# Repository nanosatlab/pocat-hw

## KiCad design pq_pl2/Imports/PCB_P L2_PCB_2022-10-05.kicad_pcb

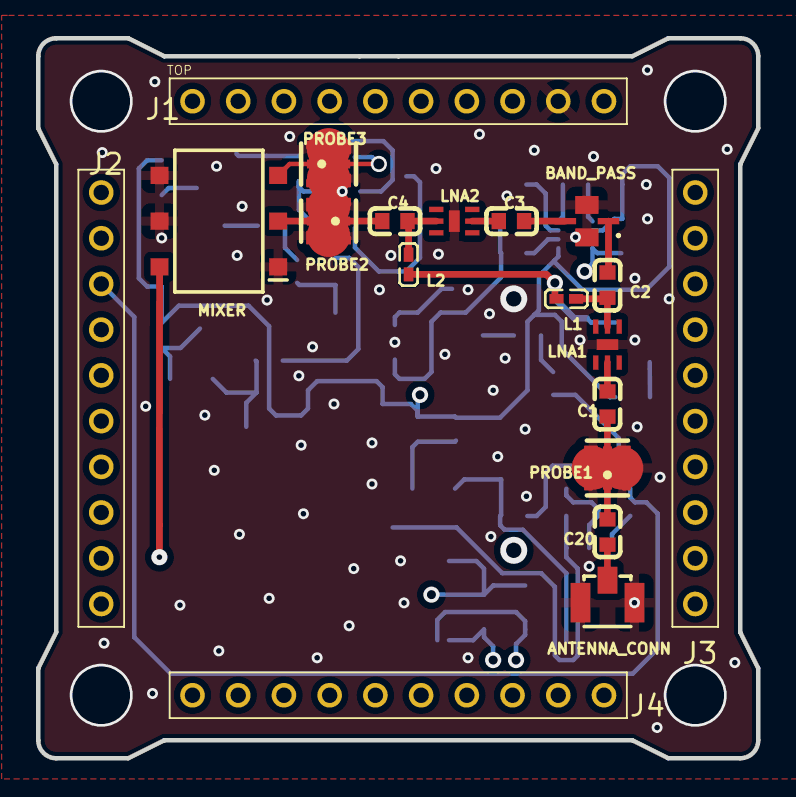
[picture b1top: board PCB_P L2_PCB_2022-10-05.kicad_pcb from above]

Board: 4 copper layers, 40.0 x 40.0 mm, 66 parts (0 on the bottom side), 47 nets.

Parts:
ANTENNA_CONN: U.FL-R-SMT-1(10); ANT-SMD_UFL-R-SMT-1-10
B3.6VIF, B3.6VRF: TPS613226ADBVT; SOT-23-5_L2.9-W1.6-P0.95-LS2.8-BR
B10V, B22V: LT1949ES8#PBF; SO-8_L4.9-W3.9-P1.27-LS5.9-BL
BAND_PASS: BFCG-162W+; BFCG162W
C1, C2, C3, C4: 10pF; C0603
C5, C6, C16, C17: 100pF; C0603
C7, C8: 330pF; C0603
C9, C10: 22u; CAPPM3216X180N
C11, C12: 10uF; C0603
C13: 1nF; C0603
C14: 1uF; C0603
C15, C20: 33nF; C0603
C18, C19: 22uF; C0603
D1, D2: MBRM120ET3G; POWERMITE_L2.0-W1.9-LS3.8-RD
J1, J2, J3, J4: SLW-110-01-T-S; SLW-110-01-X-S
L1, L2: 100nH; L0402
L3: 3.3uH; L0603
L4, L5: 10uH; L0603
L6, L7: 4.7uH; L0805
LNA1, LNA2, LNA3: LEE2-6+; SON65P200X200X105-7N
MIXER: ADE-11X+; SOTFL254P691X284-6N
OPAMP: LM258WDT; SO8
PROBE1, PROBE2, PROBE3, PROBE4: MS-156C3; IPEX-SMD_MS-156C3
R1, R2: 68K; R0603
R3: 160K; R0603
R4, R8: 10K; R0603
R5: 120K; R0603
R6, R7, R9: 20K; R0603
R10: 100K; R0603
R11: 33K; R0603
R12: 51; R0603
R13, R14: 5k; R0805
RSSI: LT5537EDDB#TRMPBF; SON50P200X300X80-9N
SAW: SF2242B; SMP-03-10 5X7 MM
TSENS: TCN75AVUA713-VAO; SOP65P490X110-8N
VCO: CVCO55CW

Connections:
3.6VIF: B3.6VIF.4, C18.2, L3.2
3.6VRF: B3.6VRF.4, C19.2, L1.2, L2.2
10V: C11.2, D1.1, R5.1, VCO.1
22V: C12.2, D2.1, OPAMP.8, R3.1
ADC_PL2: J2.2, R11.1, RSSI.8
ANTENNA_CONN_2: ANTENNA_CONN.2, C20.2
BAND_PASS_1: BAND_PASS.1, C2.2
BAND_PASS_3: BAND_PASS.3, C3.1
BOOSTER10V_1: B10V.1, R1.1
BOOSTER10V_2: B10V.2, R6.2, R7.2
BOOSTER10V_5: B10V.5, D1.2, L4.1
BOOSTER22V_1: B22V.1, R2.2
BOOSTER22V_2: B22V.2, R3.2, R4.2
BOOSTER22V_5: B22V.5, D2.2, L5.1
C1_1: C1.1, PROBE1.2
C4_2: C4.2, PROBE2.1
C5_2: C5.2, PROBE3.2
C7_1: C7.1, R1.2
C8_2: C8.2, R2.1
C17_2: C17.2, PROBE4.2, R12.2
C20_1: C20.1, PROBE1.1
DAC_PL2: J2.3, R8.2
GND: ANTENNA_CONN.1, ANTENNA_CONN.3, B3.6VIF.2, B3.6VRF.2, B10V.4, B22V.4, BAND_PASS.2, BAND_PASS.4, C7.2, C8.1, C9.2, C10.2, C11.1, C12.1, C13.2, C14.2, C16.2, C18.1, C19.1, J1.9, LNA1.7, LNA2.7, LNA3.7, MIXER.1, MIXER.4, MIXER.5, OPAMP.4, PROBE1.3, PROBE1.4, PROBE2.3, PROBE2.4, PROBE3.3, PROBE3.4, PROBE4.3, PROBE4.4, R4.1, R7.1, R9.2, R11.2, R12.1, RSSI.7, RSSI.9, SAW.1, SAW.2, SAW.3, SAW.4, SAW.6, SAW.7, SAW.8, SAW.9, TSENS.3, TSENS.4, TSENS.5, TSENS.6, TSENS.7, VCO.4
L6_2: B3.6VIF.1, L6.2
L7_2: B3.6VRF.1, L7.2
LNA1_2: C1.2, LNA1.2
LNA1_5: C2.1, L1.1, LNA1.5
LNA2_2: C3.2, LNA2.2
LNA2_5: C4.1, L2.1, LNA2.5
LNA3_2: C5.1, LNA3.2
LNA3_5: C6.2, L3.1, LNA3.5
MIXER_2: MIXER.2, PROBE2.2
MIXER_3: MIXER.3, PROBE3.1
MIXER_6: MIXER.6, VCO.2
OPAMP_2: OPAMP.2, R9.1, R10.1
OPAMP_3: OPAMP.3, R8.1
P/L_POWER: B10V.6, B22V.6, C9.1, C10.1, C13.1, C14.1, J4.5, L4.2, L5.2, L6.1, L7.1, R13.2, R14.2, RSSI.1, RSSI.6, TSENS.8
R5_2: R5.2, R6.1
RSSI_2: C17.1, RSSI.2
RSSI_3: C16.1, RSSI.3
RSSI_4: C15.1, RSSI.4
RSSI_5: C15.2, RSSI.5
SAW_5: PROBE4.1, SAW.5
SAW_10: C6.1, SAW.10
SCL: J1.2, R13.1, TSENS.2
SDA: J1.1, R14.1, TSENS.1
VCO_3: OPAMP.1, R10.2, VCO.3

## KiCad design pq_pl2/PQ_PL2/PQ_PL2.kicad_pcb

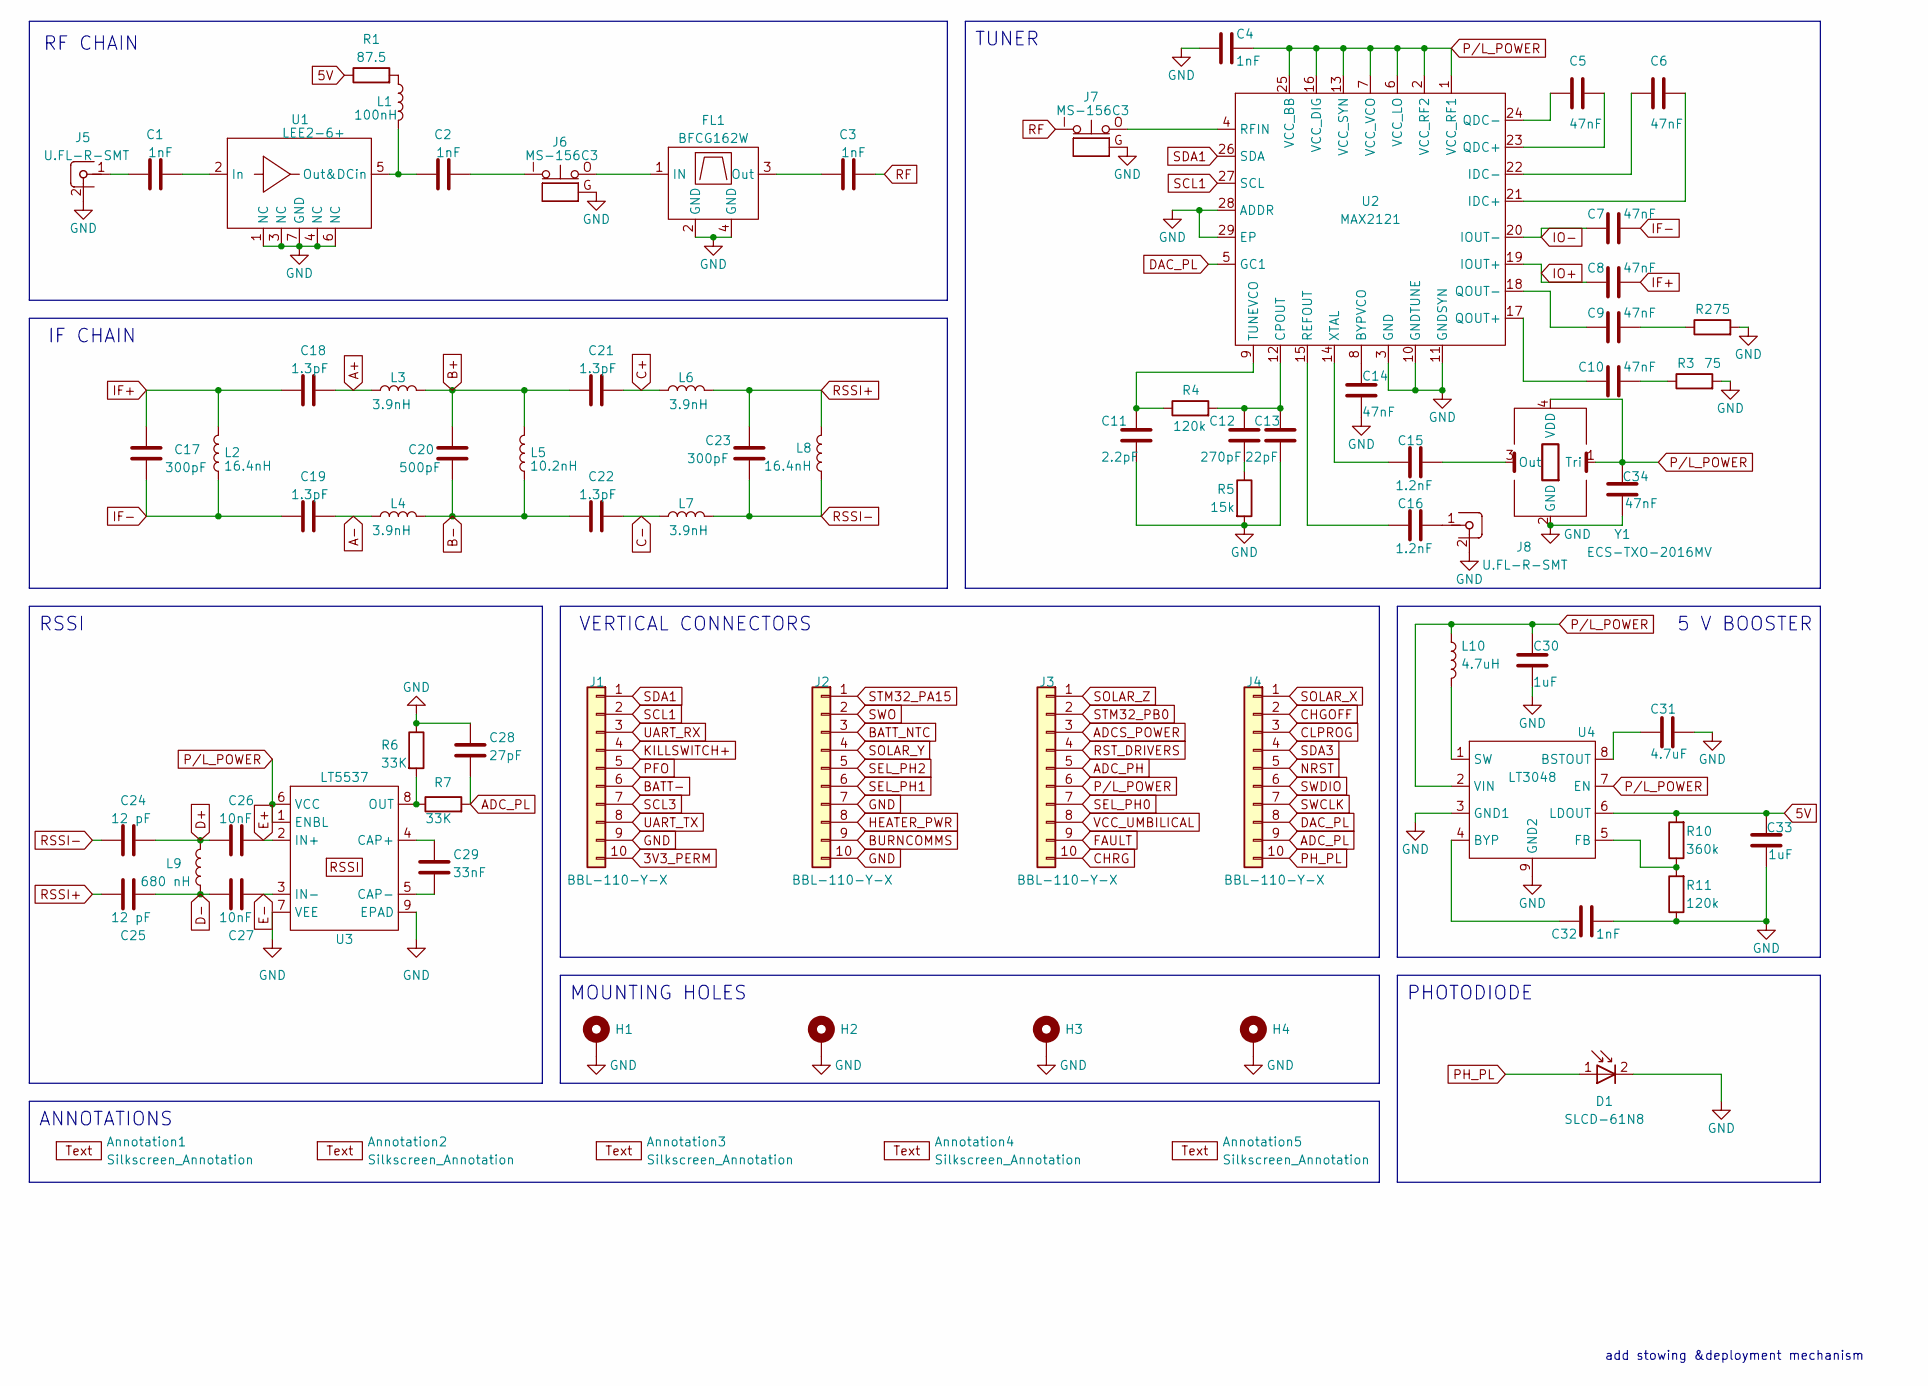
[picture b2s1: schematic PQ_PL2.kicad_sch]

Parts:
Annotation1: Silkscreen_Annotation; Bridgemaker; Manufacturer Part Numbe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 N/A
Annotation2: Silkscreen_Annotation; GRSS; Manufacturer Part Numbe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 N/A
Annotation3: Silkscreen_Annotation; NSL_long; Manufacturer Part Numbe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 N/A
Annotation4: Silkscreen_Annotation; IEEE_logo; Manufacturer Part Numbe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 N/A
Annotation5: Silkscreen_Annotation; UPC_positiu; Manufacturer Part Numbe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 N/A
C1, C2, C3, C4, C32: 1nF; C_0603_1608Metric; Manufacturer Part Numbe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 885382206005
C5, C6, C9, C10, C14, C34: 47nF; C_0603_1608Metric; Manufacturer Part Numbe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 CGA3E3X7S2A473K080AE
C7, C8: 47nF; C_0402_1005Metric; Manufacturer Part Numbe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 MAASU105SB7473KFCA01
C11: 2.2pF; C_0603_1608Metric; Manufacturer Part Numbe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 06031U2R2CAT2A
C12: 270pF; C_0603_1608Metric; Manufacturer Part Numbe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 06031A271FAT2A
C13: 22pF; C_0603_1608Metric; Manufacturer Part Numbe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 CBR06C220J5GACAUTO
C15, C16: 1.2nF; C_0603_1608Metric; Manufacturer Part Numbe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 C0603C122F1GACTU
C17, C23: 300pF; C_0402_1005Metric; Manufacturer Part Numbe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 GRT1555C1H301FA02D
C18, C19, C21, C22: 1.3pF; C_0402_1005Metric; Manufacturer Part Numbe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 CBR04C139A5GAC
C20: 500pF; C_0402_1005Metric; Manufacturer Part Numbe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 0402ZC501KAT2A
C24, C25: 12 pF; C_0402_1005Metric; Manufacturer Part Numbe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 CBR04C120F2GAC
C26, C27: 10nF; C_0402_1005Metric; Manufacturer Part Numbe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 GRM1555C1E103GE01D
C28: 27pF; C_0603_1608Metric; Manufacturer Part Numbe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 CBR04C270F2GAC
C29: 33nF; C_0603_1608Metric; Manufacturer Part Numbe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 0402YC333JAT2A
C30, C33: 1uF; C_0603_1608Metric; Manufacturer Part Numbe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 MAASA105CD7105KFCA01
C31: 4.7uF; C_0603_1608Metric; Manufacturer Part Numbe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 C1005X5R1A475K050BC
D1: SLCD-61N8; Manufacturer Part Numbe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 SLCD-61N8
FL1: BFCG162W; GE0805C-3; Manufacturer Part Numbe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 BFCG-162W+
H1, H2, H3, H4: MountingHole_Pad; MountingHole_3.2mm_M3_Pad; Manufacturer Part Numbe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 N/A
J1, J2, J3, J4: BBL-110-Y-X; Manufacturer Part Numbe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 BBL-110-Y-X
J5, J8: U.FL-R-SMT; U.FL-R-SMT-1(10); Manufacturer Part Numbe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 U.FL-R-SMT-1(10); JLCPCB PART CLASS Extended Part
J6, J7: MS-156C3; CoaxialSwitch_Hirose_MS-156C3_Horizontal; Manufacturer Part Numbe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 MS-156C3
L1: 100nH; L_0603_1608Metric; Manufacturer Part Numbe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 7447860210G
L2, L8: 16.4nH; L_0402_1005Metric; Manufacturer Part Numbe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 LQG15WZ16NG02D
L3, L4, L6, L7: 3.9nH; L_0402_1005Metric; Manufacturer Part Numbe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 LQW15AN3N9G80D
L5: 10.2nH; L_0402_1005Metric; Manufacturer Part Numbe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 LQG15WZ10NG02D
L9: 680 nH; L_0402_1005Metric; Manufacturer Part Numbe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 MLF1005GR68KT000
L10: 4.7uH; L_0603_1608Metric; Manufacturer Part Numbe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 MLF1608A3R3JTD25
R1: 87.5; R_0603_1608Metric; Manufacturer Part Numbe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 ERA-3AEB86R6V
R2, R3: 75; R_0603_1608Metric; Manufacturer Part Numbe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 TNPU060375R0BZEN0
R4: 120k; R_0603_1608Metric; Manufacturer Part Numbe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 TNPW0603120KBYEN
R5: 15k; R_0603_1608Metric; Manufacturer Part Numbe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 RP0603BRD0715KL
R6, R7: 33K; R_0603_1608Metric; Manufacturer Part Numbe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 RP0603BRD0733KL
R10: 360k; R_0603_1608Metric; Manufacturer Part Numbe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 RP0603BRD072KL
R11: 120k; R_0603_1608Metric; Manufacturer Part Numbe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 RP0603BRD072KL
U1: LEE2-6+; WSON-6-1EP_2x2mm_P0.65mm_EP1x1.6mm; Manufacturer Part Numbe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 LEE2-6+
U2: MAX2121; QFN50P500X500X80-29N; Manufacturer Part Numbe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 MAX2121
U3: LT5537; SON50P200X300X80-9N-D; Manufacturer Part Numbe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 LT5537
U4: LT3048; SON45P200X200X80-9N; Manufacturer Part Numbe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 LT3048
Y1: ECS-TXO-2016MV; ECSTXO201633320TR; Manufacturer Part Numbe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 ECS-TXO-2016MV

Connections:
3V3_PERM: J1.10
5V: C33.2, R1.1, R10.2, U4.6 (LDOUT)
A+: C18.1, L3.2
A-: C19.1, L4.2
ADCS_POWER: J3.3
ADC_PH: J3.5
ADC_PL: C28.1, J4.9, R7.2
B+: C20.2, C21.2, L3.1, L5.1
B-: C20.1, C22.2, L4.1, L5.2
BATT-: J1.6
BATT_NTC: J2.3
BURNCOMMS: J2.9
C+: C21.1, L6.2
C-: C22.1, L7.2
CHGOFF: J4.2
CHRG: J3.10
CLPROG: J4.3
D+: C24.1, C26.2, L9.2
D-: C25.1, C27.2, L9.1
DAC_PL: J4.8, U2.5 (GC1)
E+: C26.1, U3.2 (IN+)
E-: C27.1, U3.3 (IN-)
FAULT: J3.9
GND: C4.2, C11.2, C13.2, C14.2, C28.2, C30.2, C31.1, C32.1, C33.1, C34.1, D1.2, FL1.2 (GND), FL1.4 (GND), H1.1, H2.1, H3.1, H4.1, J1.9, J2.7, J2.10, J5.2, J6.G, J7.G, J8.2, R2.2, R3.2, R5.2, R6.1, R11.1, U1.1 (NC), U1.3 (NC), U1.4 (NC), U1.6 (NC), U1.7 (GND), U2.3 (GND), U2.10 (GNDTUNE), U2.11 (GNDSYN), U2.28 (ADDR), U2.29 (EP), U3.7 (VEE), U3.9 (EPAD), U4.3 (GND1), U4.9 (GND2), Y1.2 (GND); also elsewhere on the board
HEATER_PWR: J2.8
IF+: C8.1, C17.2, C18.2, L2.1
IF-: C7.1, C17.1, C19.2, L2.2
IO+: C8.2, U2.19 (IOUT+)
IO-: C7.2, U2.20 (IOUT-)
KILLSWITCH+: J1.4
NRST: J4.5
unnamed: C1.1, J5.1
unnamed: C2.2, J6.I
unnamed: C9.1, R2.1
unnamed: C10.1, R3.1
unnamed: C12.2, R5.1
unnamed: C16.2, J8.1
unnamed: FL1.1 (IN), J6.O
unnamed: C3.1, FL1.3 (Out)
unnamed: L1.1, R1.2
unnamed: C1.2, U1.2 (In)
unnamed: C2.1, L1.2, U1.5 (Out&DCin)
unnamed: C14.1, U2.8 (BYPVCO)
unnamed: C12.1, C13.1, R4.2, U2.12 (CPOUT)
unnamed: C6.1, U2.21 (IDC+)
unnamed: C6.2, U2.22 (IDC-)
unnamed: C5.1, U2.23 (QDC+)
unnamed: C5.2, U2.24 (QDC-)
unnamed: C10.2, U2.17 (QOUT+)
unnamed: C9.2, U2.18 (QOUT-)
unnamed: C16.1, U2.15 (REFOUT)
unnamed: J7.O, U2.4 (RFIN)
unnamed: C11.1, R4.1, U2.9 (TUNEVCO)
unnamed: C15.1, U2.14 (XTAL)
unnamed: C29.2, U3.4 (CAP+)
unnamed: C29.1, U3.5 (CAP-)
unnamed: R6.2, R7.1, U3.8 (OUT)
unnamed: C31.2, U4.8 (BSTOUT)
unnamed: C32.2, U4.4 (BYP)
unnamed: R10.1, R11.2, U4.5 (FB)
unnamed: L10.2, U4.1 (SW)
unnamed: C15.2, Y1.3 (Out)
PFO: J1.5
PH_PL: D1.1, J4.10
P/L_POWER: C4.1, C30.1, C34.2, J3.6, L10.1, U2.1 (VCC_RF1), U2.2 (VCC_RF2), U2.6 (VCC_LO), U2.7 (VCC_VCO), U2.13 (VCC_SYN), U2.16 (VCC_DIG), U2.25 (VCC_BB), U3.1 (ENBL), U3.6 (VCC), U4.2 (VIN), U4.7 (EN), Y1.1 (Tri), Y1.4 (VDD); also elsewhere on the board
RF: C3.2, J7.I
RSSI+: C23.2, C25.2, L6.1, L8.1
RSSI-: C23.1, C24.2, L7.1, L8.2
RST_DRIVERS: J3.4
SCL1: J1.2, U2.27 (SCL)
SCL3: J1.7
SDA1: J1.1, U2.26 (SDA)
SDA3: J4.4
SEL_PH0: J3.7
SEL_PH1: J2.6
SEL_PH2: J2.5
SOLAR_X: J4.1
SOLAR_Y: J2.4
SOLAR_Z: J3.1
STM32_PA15: J2.1
STM32_PB0: J3.2; also elsewhere on the board
SWCLK: J4.7
SWDIO: J4.6
SWO: J2.2
UART_RX: J1.3
UART_TX: J1.8
VCC_UMBILICAL: J3.8

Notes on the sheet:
add stowing &deployment mechanism
VERTICAL CONNECTORS
MOUNTING HOLES
IF CHAIN
5 V BOOSTER
RF CHAIN
TUNER
RSSI
ANNOTATIONS
PHOTODIODE

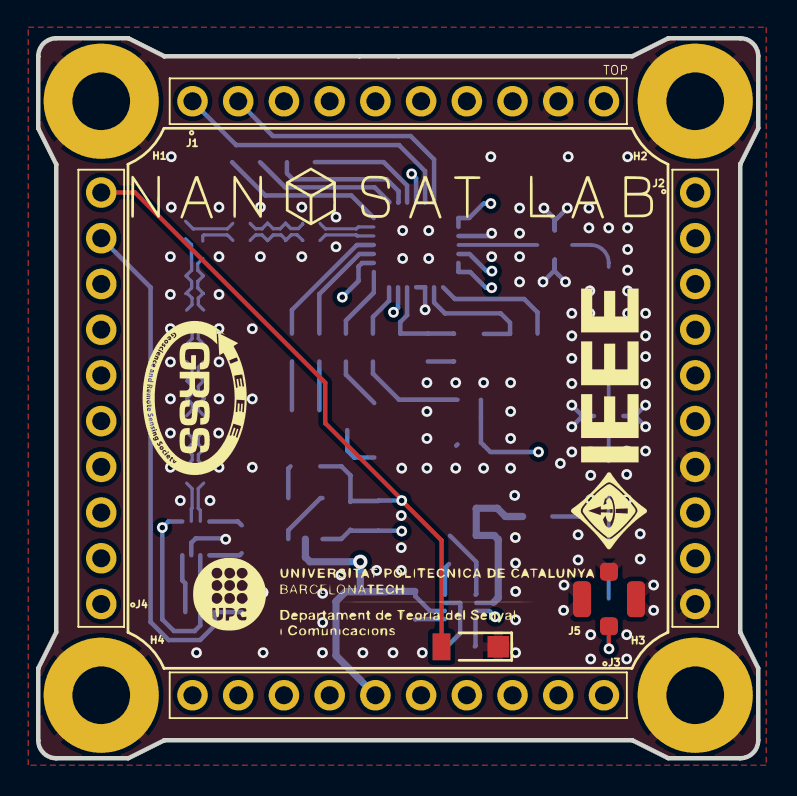
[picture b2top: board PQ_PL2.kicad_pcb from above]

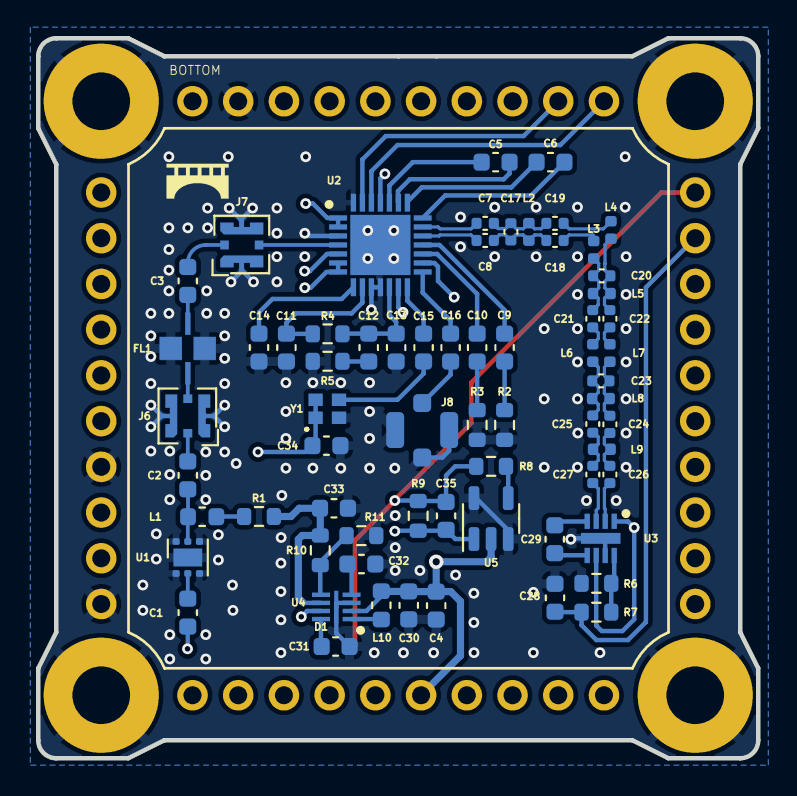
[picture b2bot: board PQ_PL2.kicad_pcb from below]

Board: 4 copper layers, 40.0 x 40.0 mm, 81 parts (67 on the bottom side), 59 nets.

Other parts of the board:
C35: 100 pF; C_0603_1608Metric
R8: 100; R_0603_1608Metric
R9: 2k; R_0603_1608Metric
U5: TL071; TSOT-23-5

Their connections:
GND: U5.3 (+), U5.5 (V+); also elsewhere on the board
unnamed: C35.2, R8.2, R9.1
unnamed: R8.1, U5.4 (-)
P/L_POWER: U5.2 (V-); also elsewhere on the board
STM32_PB0: C35.1, R9.2, U5.1; also elsewhere on the board

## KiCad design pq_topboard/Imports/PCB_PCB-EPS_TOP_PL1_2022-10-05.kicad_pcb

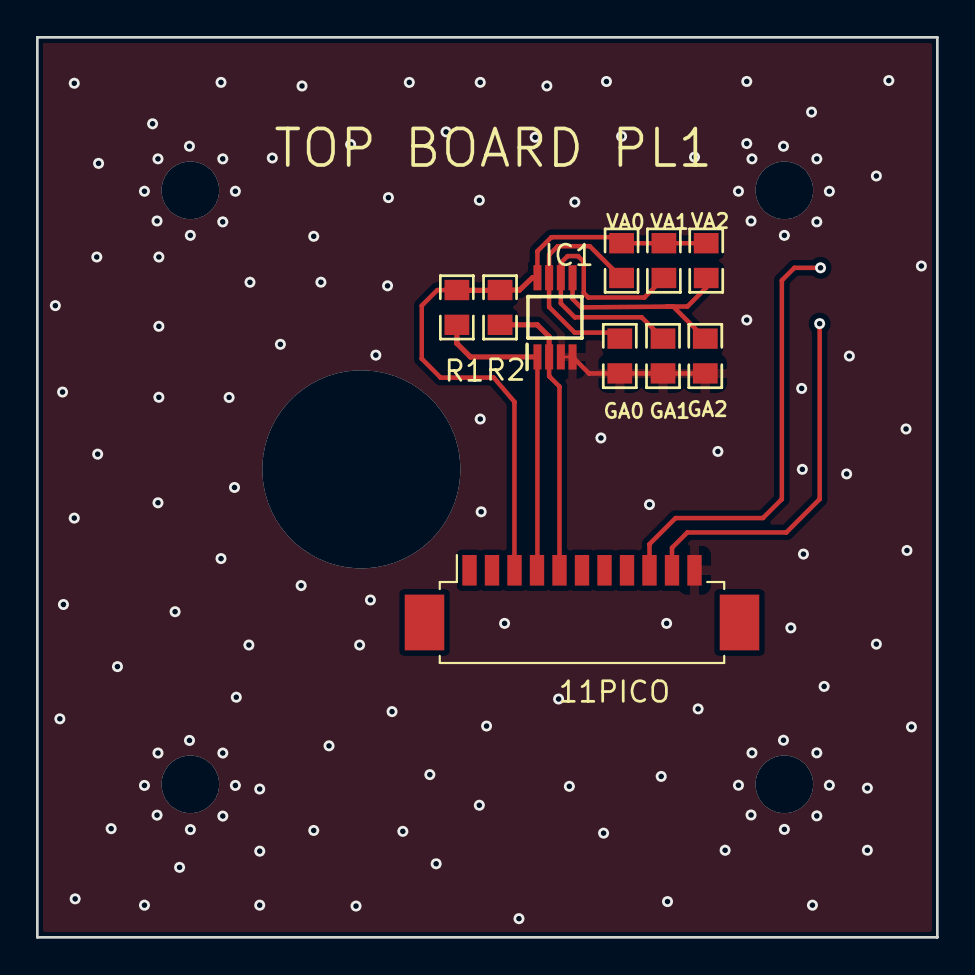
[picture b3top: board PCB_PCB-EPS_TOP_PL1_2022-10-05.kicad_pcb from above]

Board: 2 copper layers, 50.0 x 50.0 mm, 11 parts (0 on the bottom side), 9 nets.

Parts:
11PICO: REF; MOLEX_PICOBLADE_53261-1171_11X1.25MM_ANGLED
GA0, GA1, GA2: 5k; R0805
IC1: TCN75AVUA713-VAO; SOP65P490X110-8N
PHT: SLCD-61N8
R1, R2: 5k; R0805
VA0, VA1, VA2: 5k; R0805

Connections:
GND: 11PICO.11, GA0.1, GA1.1, GA2.1, IC1.3, IC1.4
IC1_5: GA2.2, IC1.5, VA2.1
IC1_6: GA1.2, IC1.6, VA1.1
IC1_7: GA0.2, IC1.7, VA0.1
PHOTODIODE: 11PICO.10, PHT.1
PHOTODIODE_GND: 11PICO.9, PHT.2
SCL: 11PICO.5, IC1.2, R2.1
SDA: 11PICO.4, IC1.1, R1.1
VCC: 11PICO.3, IC1.8, R1.2, R2.2, VA0.2, VA1.2, VA2.2

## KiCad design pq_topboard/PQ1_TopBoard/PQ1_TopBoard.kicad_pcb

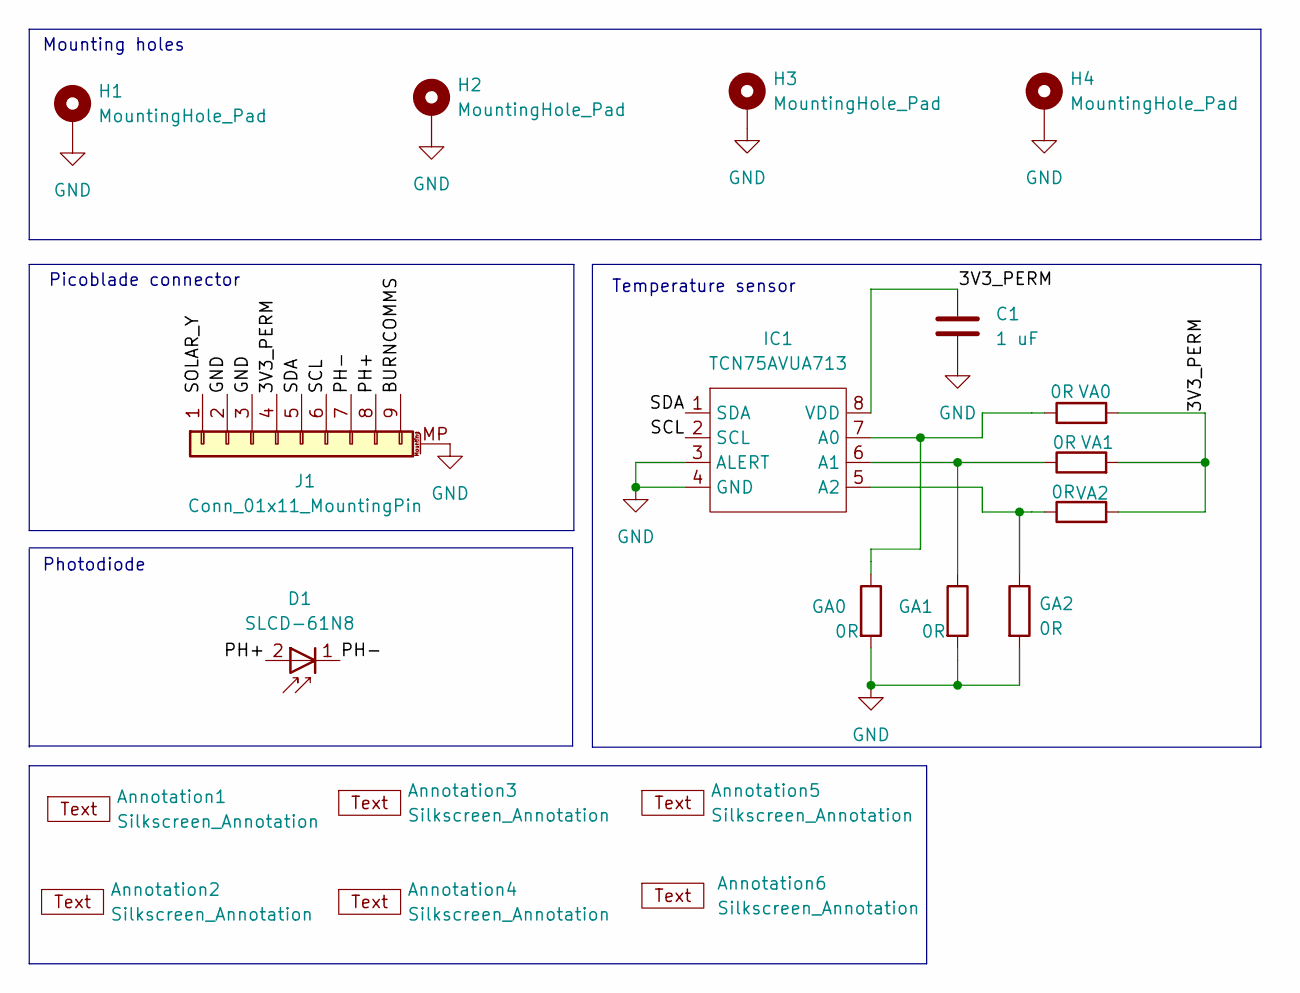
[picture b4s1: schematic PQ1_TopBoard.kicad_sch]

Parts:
Annotation1: Silkscreen_Annotation; IEEE_logo
Annotation2: Silkscreen_Annotation; GRSS
Annotation3: Silkscreen_Annotation; NSL_long
Annotation4: Silkscreen_Annotation; Telecos
Annotation5: Silkscreen_Annotation; UPC_positiu
Annotation6: Silkscreen_Annotation; NSL_Lektron
C1: 1 uF; C_0603_1608Metric; Manufacturer Part Numbe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 GRM188R72A104KA35J
D1: SLCD-61N8; Manufacturer Part Numbe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 SLCD-61N8
GA0, GA1, GA2: 0R; R_0805_2012Metric; Manufacturer Part Numbe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 CRCW08055K00JNTA
H1, H2, H3, H4: MountingHole_Pad; MountingHole_3.2mm_M3_ISO14580_Pad; Manufacturer Part Numbe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 N/A
IC1: TCN75AVUA713; TCN75AVOA; Manufacturer Part Numbe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 TCN75AVOA
J1: Conn_01x11_MountingPin; Molex_PicoBlade_53261-0971_1x09-1MP_P1.25mm_Horizontal; Manufacturer Part Numbe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 Picoblade-53261-0971
VA0, VA1, VA2: 0R; R_0805_2012Metric; Manufacturer Part Numbe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 CRCW08055K00JNTA

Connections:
/3V3_PERM: C1.1, IC1.8 (VDD), J1.4, VA0.2, VA1.2, VA2.2
/BURNCOMMS: J1.9
/PH+: D1.2, J1.8
/PH-: D1.1, J1.7
/SCL: IC1.2 (SCL), J1.6
/SDA: IC1.1 (SDA), J1.5
/SOLAR_Y: J1.1
GND: C1.2, GA0.2, GA1.2, GA2.2, H1.1, H2.1, H3.1, H4.1, IC1.3 (ALERT), IC1.4 (GND), J1.2, J1.3, J1.MP (MountPin)
unnamed: GA0.1, IC1.7 (A0), VA0.1
unnamed: GA1.1, IC1.6 (A1), VA1.1
unnamed: GA2.1, IC1.5 (A2), VA2.1

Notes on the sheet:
Photodiode
Picoblade connector
Mounting holes
Temperature sensor

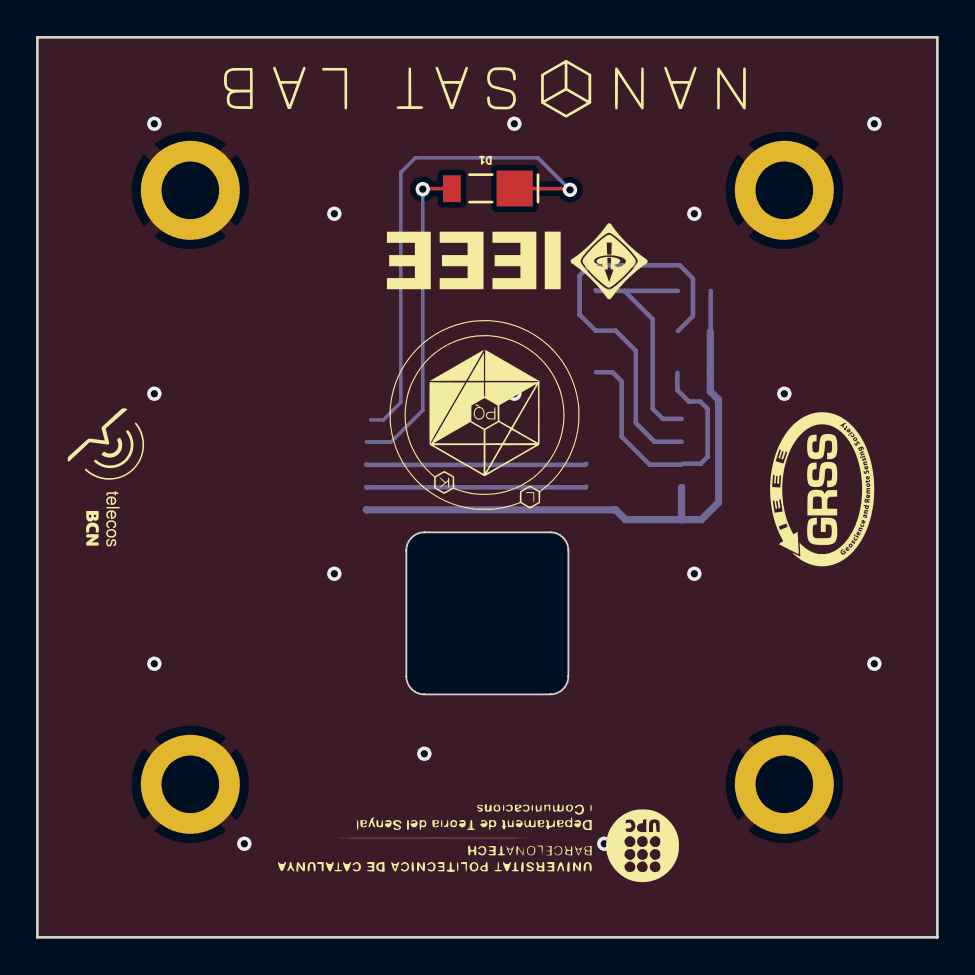
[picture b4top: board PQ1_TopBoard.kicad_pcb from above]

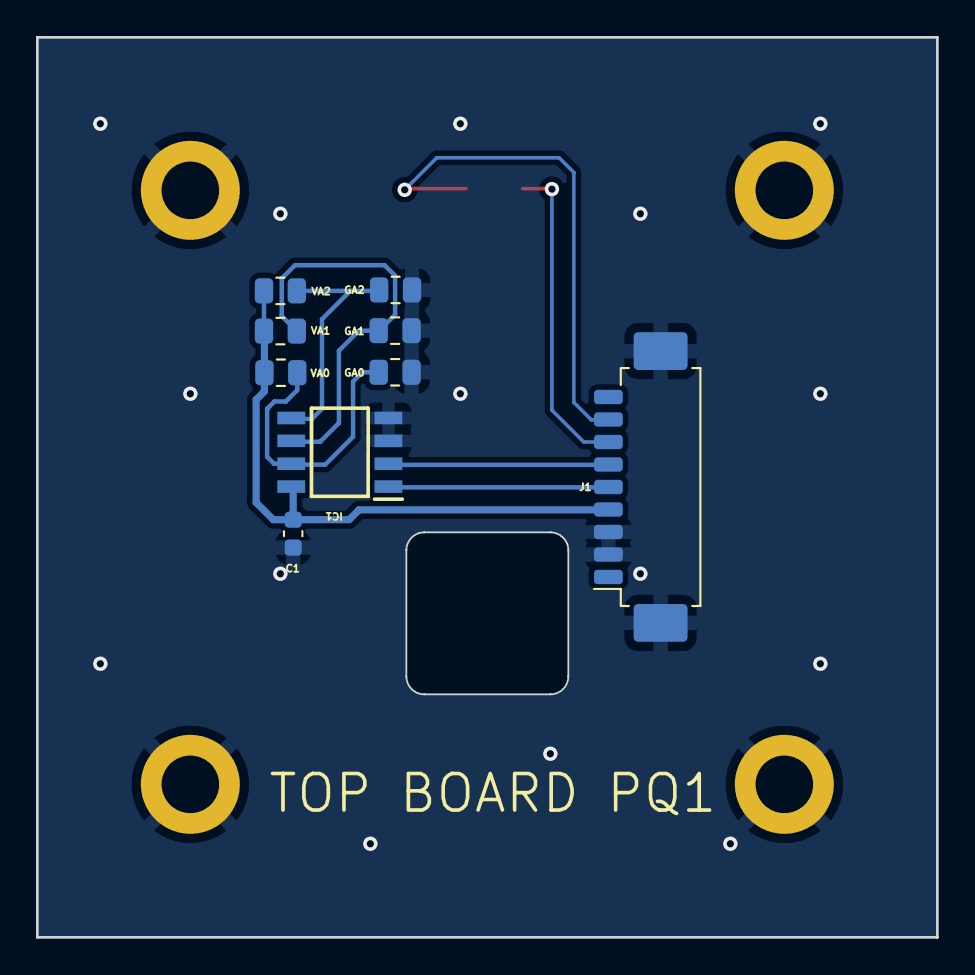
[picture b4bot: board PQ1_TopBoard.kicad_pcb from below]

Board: 2 copper layers, 50.0 x 50.0 mm, 20 parts (9 on the bottom side), 9 nets.
